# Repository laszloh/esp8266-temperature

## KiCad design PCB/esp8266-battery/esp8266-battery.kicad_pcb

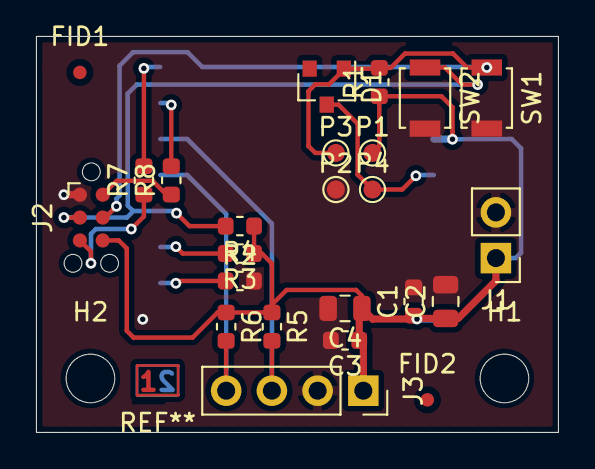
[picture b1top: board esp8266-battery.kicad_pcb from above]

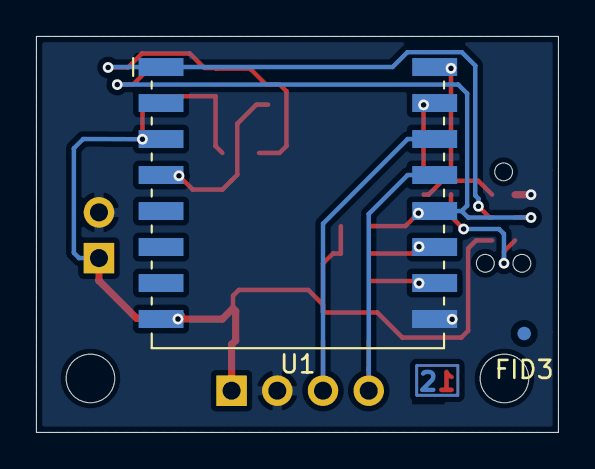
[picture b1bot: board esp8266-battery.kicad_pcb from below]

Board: 2 copper layers, 29.0 x 22.0 mm, 28 parts (2 on the bottom side), 13 nets.

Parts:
C1, C3: 100n; C_0603_1608Metric
C2, C4: 10u; C_0805_2012Metric
D1: BAT-85; D_SOT-23_ANK
FID1, FID2, FID3: Fiducial; Fiducial_0.75mm_Mask1.5mm
H1, H2: MountingHole_Pad; MountingHole_2.7mm_M2.5
J1: 2xAA; PinHeader_1x02_P2.54mm_Vertical
J2: program; Tag-Connect_TC2030-IDC-NL_2x03_P1.27mm_Vertical
J3: BME280 modul; PinSocket_1x04_P2.54mm_Vertical
P1, P2, P3, P4: ICT-Point; TestPoint_Pad_D1.0mm
R1, R2, R3, R4: 10k; R_0603_1608Metric
R5, R6: 1.5k; R_0603_1608Metric
R7, R8: 220R; R_0603_1608Metric
SW1: reset; SW_SPST_B3U-1000P
SW2: boot; SW_SPST_B3U-1000P
U1: ESP-07

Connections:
+3V3: C1.1, C2.1, C3.1, C4.1, J1.1, J2.6, J3.1, P1.1, R1.1, R3.1, R4.1, R5.1, R6.1, U1.3, U1.8
/I2C-SCL: J3.3, R5.2, U1.14
/I2C-SDA: J3.4, R6.2, U1.13
/IO0: J2.3, R4.2, SW2.1, U1.12
/RXD: J2.5, R7.1
/TXD: J2.2, R8.1
/~RST: D1.2, J2.4, P3.1, R1.2, SW1.1, U1.1
GND: C1.2, C2.2, C3.2, C4.2, J1.2, J2.1, J3.2, P2.1, R2.2, SW1.2, SW2.2, U1.9
unnamed: D1.1, P4.1, U1.4
unnamed: R2.1, U1.10
unnamed: R3.2, U1.11
unnamed: R7.2, U1.16
unnamed: R8.2, U1.15

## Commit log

2020-09-13 Add ignore files for KiCAD, FrreCAD and LTSpice
2020-09-13 Add schematic and PCB for battery nodes
    Added the schematic and PCB for the battery driven nodes using an ESP-07
    and BME280
2020-09-13 Add Software framework
    Add the first Software design. This is as of now untested.
2020-09-14 Update layout to final version
2020-09-14 Add missing 3D models
2020-09-14 Prepare for Housing desing
2020-09-15 Design bottom housing part with battery compartment
2020-09-16 Add housing parts and assembly
    Create the top and bottom shell and add an assembly for the two parts with the batteries and the PCB.
2020-09-29 squash me if you can
2020-10-02 Software work
2020-10-03 software finished
2020-10-05 text
2020-10-09 Add BMP180 sensor support
2020-10-11 add update to wifimanager
    add update to wifimanager and tripple-reset for enter setup
2020-10-11 squash candidate
2020-10-12 software updates
2020-10-12 squash me
2020-10-13 fixes needed
2020-10-13 wqert
2020-10-13 esp8266 implelemntation of NVS working
2020-10-16 qwert
2020-10-20 wüp wüp
2020-10-23 Cleanup and fix in comment section
2020-10-23 Mehhhh....
2020-10-28 blubb
2020-10-30 working
2020-10-31 Hack templates some moare
2020-10-31 Composer
2020-10-31 Change the debug connector to TC2030-6
2020-11-02 Use LittleFs instead of ported NVS
2020-11-02 Software works again.
2020-11-04 Change WifiManager to upstream development version
2020-11-04 Add formware upgrade functionalities
2021-01-28 Wifi update
